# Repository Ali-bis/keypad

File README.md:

The Void Macro Pad\

This custom 3x3 mechanical keypad was designed to give me a speed boost in Blender and coding. It's built around CircuitPython so I can easily remap the keys without worrying about messing with the code.

Below is a 3D render showing the PCB mounted inside the proposed 3D-printed enclosure (Outer_Case_1.stl). The board dimensions (approx 100mm x 75mm) are designed to fit flush within the case walls, allowing space for the USB-C connector at the top.

Why I wanted to build this\

I got tired of having to remember a million key combos for simple tasks like Saving, Undoing, and Rendering. It was really slowing me down. Plus I had a hankering to learn how to design a PCB from scratch using the Seeed XIAO board. (Also, I thought it would be a blast!)

How does it work\

The brain of this operation is a Seeed XIAO RP2040. It's connected up to 9 mechanical switches (I'm a fan of Cherry MX) laid out in a matrix. The details are below...

Firmware: I'm running KMK (CircuitPython keyboard library) to make it all work.\

Features: When hooked up to a computer it's a pretty standard USB HID keyboard. I also snuck in a rotary encoder which lets me control volume and zoom with a nifty little wheel.

The Parts\

Controller: Seeed XIAO RP2040\

Switches: 9 x Cherry MX Blue switches\

Diodes: 9 x 1N4148 (just in case I didn't want to deal with ghosting on my keyboard)\

Encoder: EC11 Rotary Encoder

Status\

The PCB design is done and now I'm just waiting on the boards to arrive. Once they do, I'll be able to pop in some switches and 3D print the case.

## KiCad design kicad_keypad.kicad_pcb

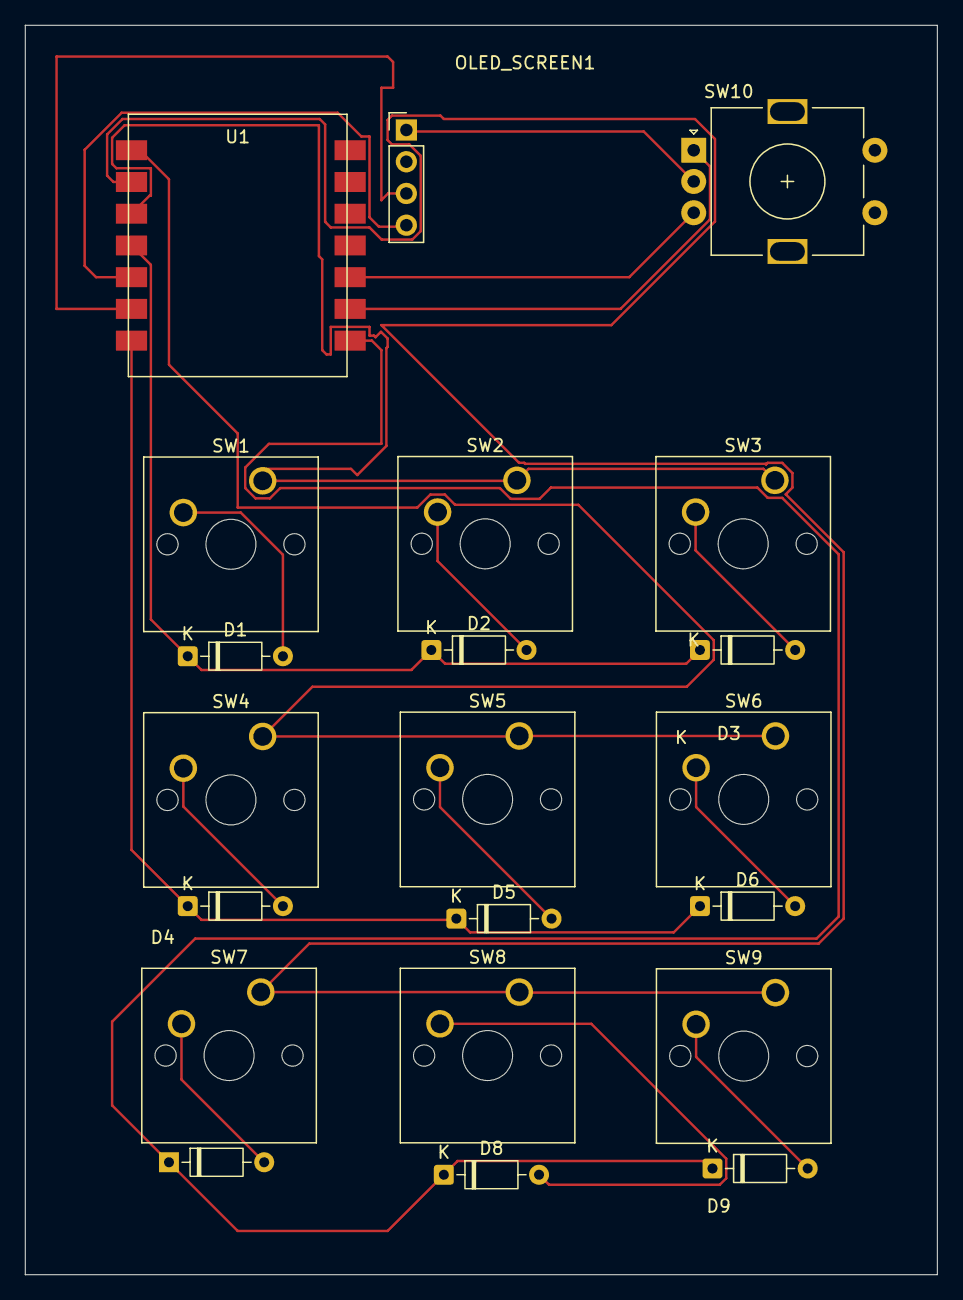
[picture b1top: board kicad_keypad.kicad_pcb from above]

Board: 2 copper layers, 73.0 x 100.0 mm, 21 parts (0 on the bottom side), 20 nets.

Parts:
D1, D2, D3, D4, D5, D6, D7, D8, D9: D_Small; D_DO-35_SOD27_P7.62mm_Horizontal
OLED_SCREEN1: Conn_01x04_Pin; PinHeader_1x04_P2.54mm_Vertical
SW1, SW2, SW3, SW4, SW5, SW6, SW7, SW8, SW9: MX_Switch; SW_Cherry_MX_1.00u_PCB
SW10: RotaryEncoder_Switch; RotaryEncoder_Alps_EC11E-Switch_Vertical_H20mm
U1: XIAO_RP2040; XIAO-RP2040-SMD

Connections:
GND: OLED_SCREEN1.1, SW10.C
unnamed: D1.2 (A), SW1.2
unnamed: D1.1 (K), D2.1 (K), D3.1 (K), U1.4 (P3_D3)
unnamed: D2.2 (A), SW2.2
unnamed: D3.2 (A), SW3.2
unnamed: D4.2 (A), SW4.2
unnamed: D4.1 (K), D5.1 (K), D6.1 (K), U1.7 (P6_TX)
unnamed: D5.2 (A), SW5.2
unnamed: D6.2 (A), SW6.2
unnamed: D7.2 (A), SW7.2
unnamed: D7.1 (K), D8.1 (K), D9.1 (K), U1.8 (P7_RX)
unnamed: D8.2 (A), SW8.2
unnamed: D9.2 (A), SW9.2
unnamed: OLED_SCREEN1.3, U1.6 (P5_SCL)
unnamed: OLED_SCREEN1.4, U1.5 (P4_SDA)
unnamed: SW4.1, SW5.1, SW6.1, U1.1 (P0_D0)
unnamed: SW7.1, SW8.1, SW9.1, U1.2 (P1_D1)
unnamed: SW1.1, SW2.1, SW3.1, U1.3 (P2_D2)
unnamed: SW10.A, U1.9 (P8_SCK)
unnamed: SW10.B, U1.10 (P9_MISO)

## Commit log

2025-12-18 Rename kicad_keypad.csv to BOM_kicad_keypad.csv
2025-12-18 Rename kicad_keypad.step to cad/kicad_keypad.step
2025-12-18 Rename Screenshot 2025-12-18 151251.png to images/Screenshot 2025-12-18 151251.png
2025-12-18 Rename Screenshot 2025-12-18 151543.png to images/Screenshot 2025-12-18 151543.png
2025-12-18 Rename Screenshot 2025-12-18 151251.png to pic1
2025-12-18 Rename Screenshot 2025-12-18 151543.png to pic2
2025-12-19 Rename Cover.stl to casing&stepmodels/Cover.stl
2025-12-19 Rename Outer_Case_1.stl to casing&stepmodels/Outer_Case_1.stl
2025-12-19 Rename Cover.stl to Cover.stl
2025-12-19 Rename Outer_Case_1.stl to Outer_Case_1.stl
